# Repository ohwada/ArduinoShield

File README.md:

Arduino Shield
===============

Eagle data for Milling machine <br>
Arduino skech <br>

### LED 3x3 Matrix No1
https://github.com/ohwada/ArduinoShield/tree/master/docs/led_3x3_1/ <br>

### LED 3x3 Matrix No2
https://github.com/ohwada/ArduinoShield/tree/master/docs/led_3x3_2/ <br>

### LED 3x3 Matrix No3
https://github.com/ohwada/ArduinoShield/tree/master/docs/led_3x3_3/ <br>

### Seven-Segment LED - SND2537
https://github.com/ohwada/ArduinoShield/tree/master/docs/7seg_snd2537/ <br>

### LED Button controlled by Serial
https://github.com/ohwada/ArduinoShield/tree/master/docs/led_button_1/ <br>

### ESP8266 CEREVO 
https://github.com/ohwada/ArduinoShield/tree/master/docs/led_button_1/ <br>

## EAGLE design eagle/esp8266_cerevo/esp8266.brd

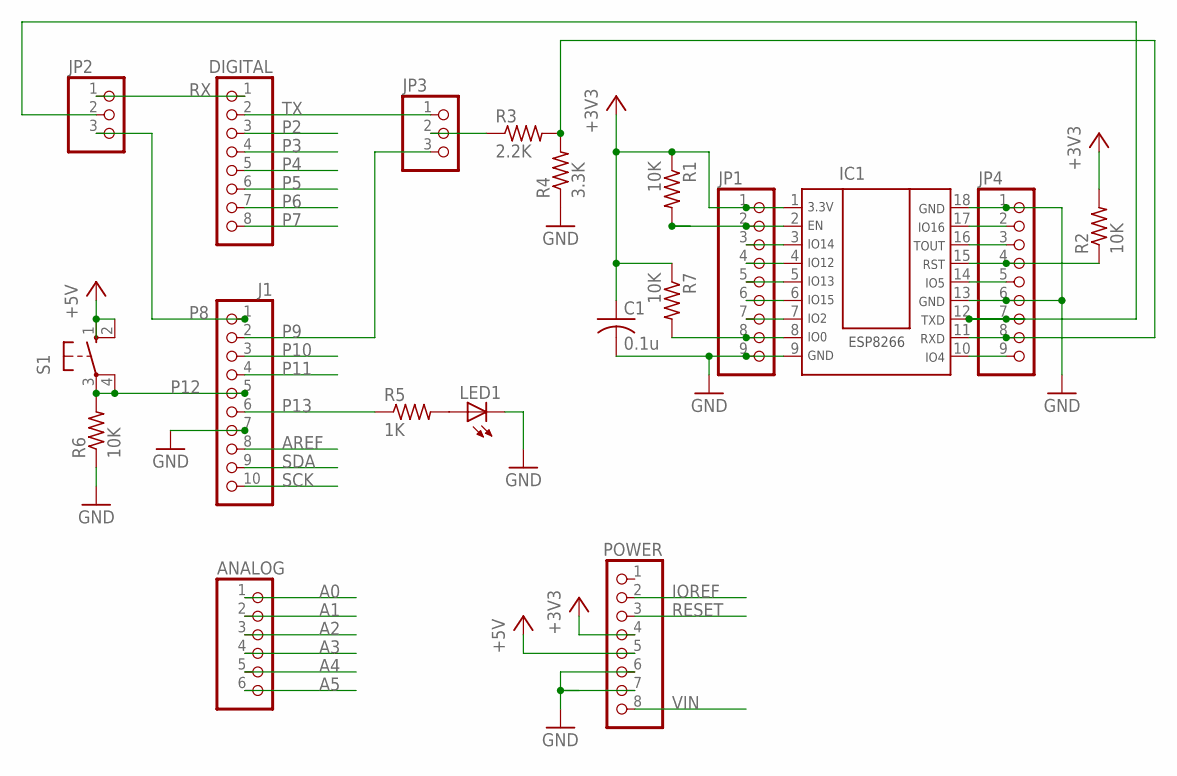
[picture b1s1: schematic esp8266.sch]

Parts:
ANALOG: PINHD-1X6; 1X06
C1: 0.1u; C050-025X075
DIGITAL: PINHD-1X8TH; 1X08-TH
IC1: ESP8266; CEREVO-PKG
J1: PINHD-1X10TH; 1X10-TH
JP1, JP4: PINHD-1X9; 1X09
JP2, JP3: PINHD-1X3; 1X03
LED1: LED3MM
POWER: PINHD-1X8TH; 1X08-TH
R1, R2, R6, R7: 10K; 0207/10
R3: 2.2K; 0207/10
R4: 3.3K; 0207/10
R5: 1K; 0207/10
S1: 10-XX; B3F-10XX

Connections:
+3V3: C1.1, IC1.1, JP1.1, POWER.4, R1.1, R2.2, R7.1
+5V: POWER.5, S1.1 (S), S1.2 (S1)
A0: ANALOG.1
A1: ANALOG.2
A2: ANALOG.3
A3: ANALOG.4
A4: ANALOG.5
A5: ANALOG.6
AREF: J1.8
GND: C1.2, IC1.9, IC1.13, IC1.18, J1.7, JP1.9, JP4.1, JP4.6, LED1.K (C), POWER.6, POWER.7, R4.1, R6.1
IOREF: POWER.2
unnamed: IC1.11, JP4.8, R3.2, R4.2
unnamed: LED1.A, R5.2
unnamed: JP3.2, R3.1
unnamed: IC1.12, JP2.2, JP4.7
unnamed: IC1.2, JP1.2, R1.2
unnamed: IC1.15, JP4.4, R2.1
unnamed: IC1.3, JP1.3
unnamed: IC1.4, JP1.4
unnamed: IC1.5, JP1.5
unnamed: IC1.6, JP1.6
unnamed: IC1.7, JP1.7
unnamed: IC1.8, JP1.8, R7.2
unnamed: IC1.10, JP4.9
unnamed: IC1.17, JP4.2
unnamed: IC1.16, JP4.3
unnamed: IC1.14, JP4.5
P2: DIGITAL.3
P3: DIGITAL.4
P4: DIGITAL.5
P5: DIGITAL.6
P6: DIGITAL.7
P7: DIGITAL.8
P8: J1.1, JP2.3
P9: J1.2, JP3.3
P10: J1.3
P11: J1.4
P12: J1.5, R6.2, S1.3, S1.4 (P1)
P13: J1.6, R5.1
RESET: POWER.3
RX: DIGITAL.1, JP2.1
SCK: J1.10
SDA: J1.9
TX: DIGITAL.2, JP3.1
VIN: POWER.8

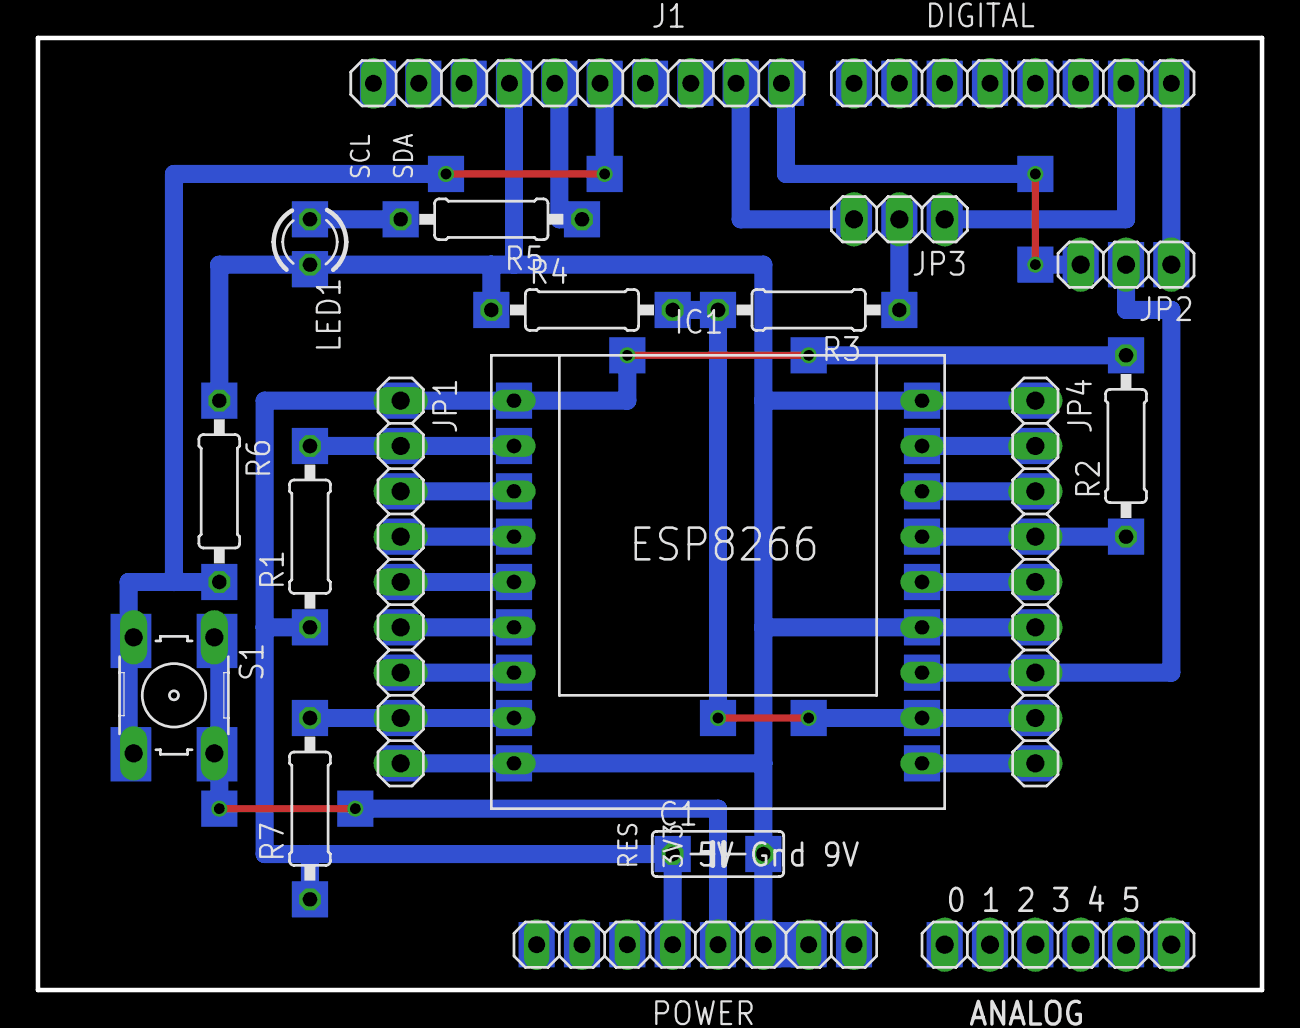
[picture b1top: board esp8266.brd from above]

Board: 2 copper layers, 68.6 x 53.3 mm, 19 parts (0 on the bottom side), 25 nets.

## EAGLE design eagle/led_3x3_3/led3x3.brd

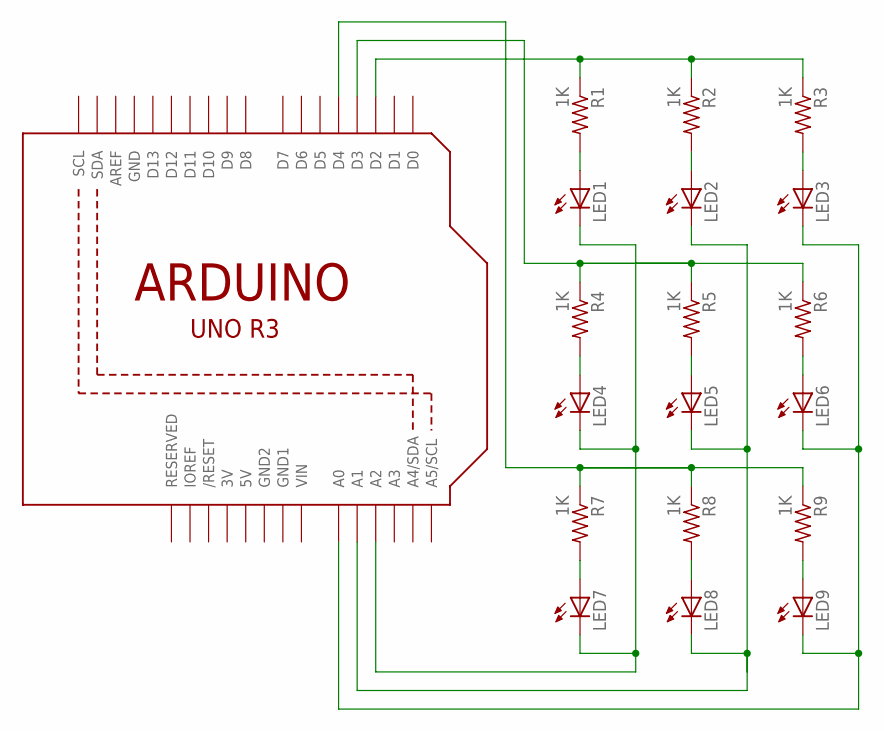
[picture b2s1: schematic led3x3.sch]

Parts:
LED1, LED2, LED3, LED4, LED5, LED6, LED7, LED8, LED9: LED5MM
R1, R2, R3, R4, R5, R6, R7, R8, R9: 1K; 0207/10
U1: ARDUINOR3-BPLACE

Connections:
3V: U1.3V
5V: U1.5V
D3: R4.1, R5.1, R6.1, U1.D3
GND: U1.GND
GND1: U1.GND1
GND2: U1.GND2
unnamed: LED3.K (C), LED6.K (C), LED9.K (C), U1.A0
unnamed: LED1.A, R1.2
unnamed: LED2.K (C), LED5.K (C), LED8.K (C), U1.A1
unnamed: R1.1, R2.1, R3.1, U1.D2
unnamed: LED2.A, R2.2
unnamed: R7.1, R8.1, R9.1, U1.D4
unnamed: LED1.K (C), LED4.K (C), LED7.K (C), U1.A2
unnamed: LED3.A, R3.2
unnamed: LED4.A, R4.2
unnamed: LED5.A, R5.2
unnamed: LED6.A, R6.2
unnamed: LED7.A, R7.2
unnamed: LED8.A, R8.2
unnamed: LED9.A, R9.2
VIN: U1.VIN

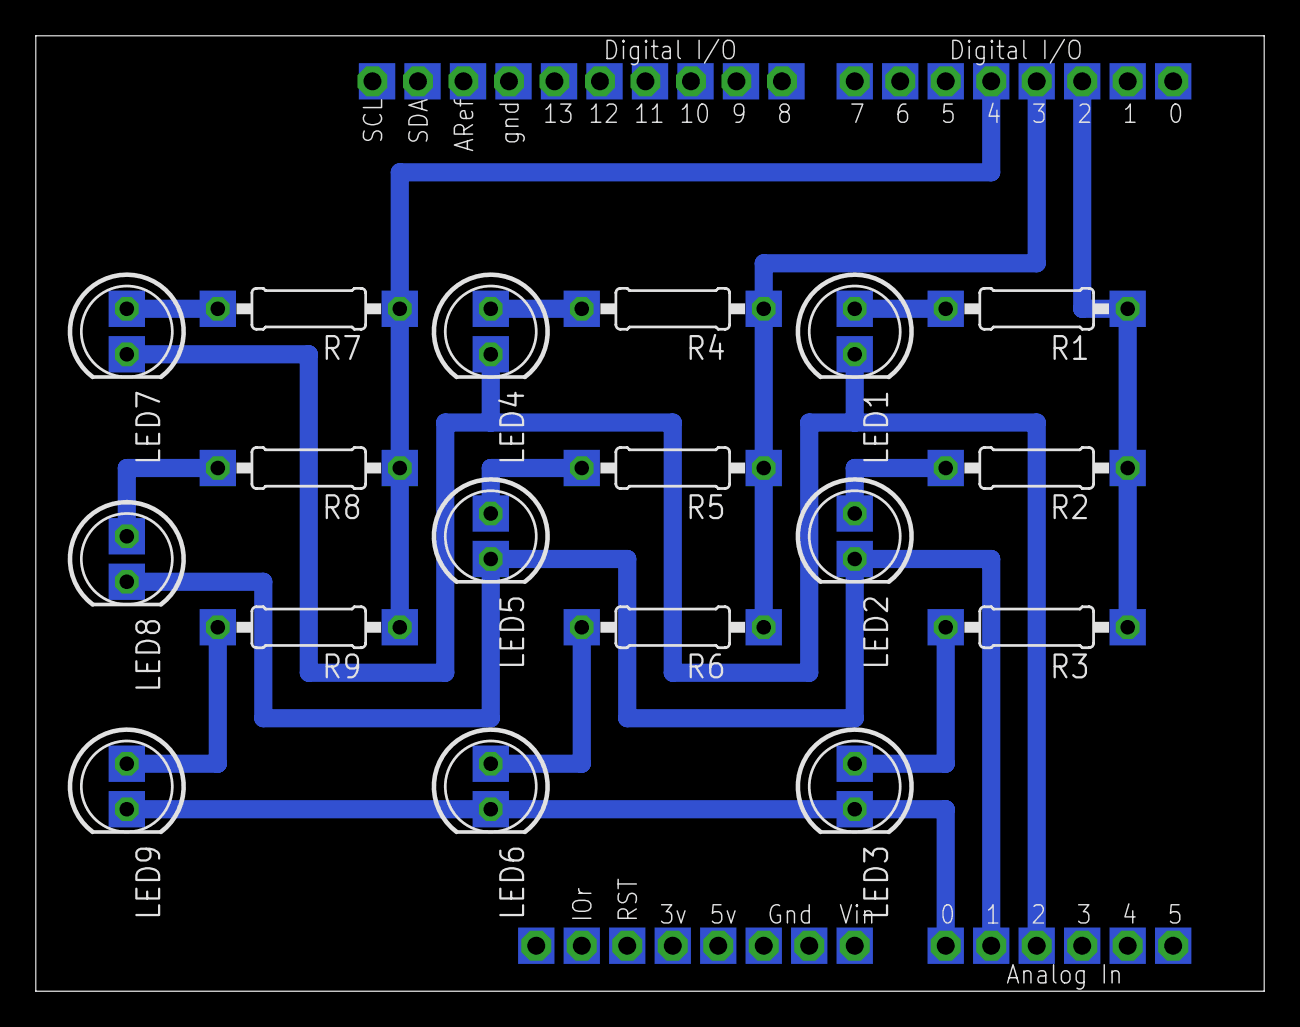
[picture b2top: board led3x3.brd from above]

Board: 2 copper layers, 68.6 x 53.3 mm, 19 parts (0 on the bottom side), 15 nets.

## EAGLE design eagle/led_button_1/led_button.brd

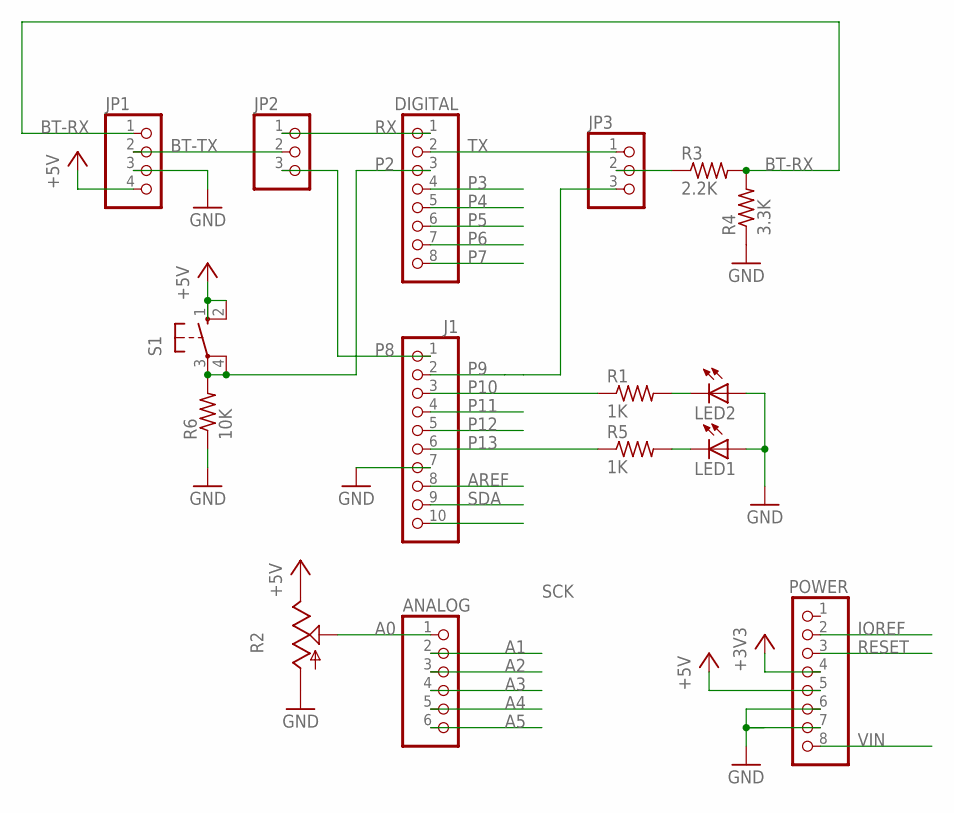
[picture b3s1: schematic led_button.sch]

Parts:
ANALOG: PINHD-1X6; 1X06
DIGITAL: PINHD-1X8TH; 1X08-TH
J1: PINHD-1X10TH; 1X10-TH
JP1: PINHD-1X4; 1X04
JP2, JP3: PINHD-1X3; 1X03
LED1, LED2: LED3MM
POWER: PINHD-1X8TH; 1X08-TH
R1, R5: 1K; 0207/10
R2: TRIM_US-B25P; B25P
R3: 2.2K; 0207/10
R4: 3.3K; 0207/10
R6: 10K; 0207/10
S1: 10-XX; B3F-10XX

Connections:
+3V3: POWER.4
+5V: JP1.4, POWER.5, R2.E, S1.1 (S), S1.2 (S1)
A0: ANALOG.1, R2.S
A1: ANALOG.2
A2: ANALOG.3
A3: ANALOG.4
A4: ANALOG.5
A5: ANALOG.6
AREF: J1.8
BT-RX: JP1.1, R3.2, R4.2
BT-TX: JP1.2, JP2.2
GND: J1.7, JP1.3, LED1.A, LED2.A, POWER.6, POWER.7, R2.A, R4.1, R6.1
IOREF: POWER.2
unnamed: LED1.K (C), R5.2
unnamed: JP3.2, R3.1
unnamed: LED2.K (C), R1.2
P2: DIGITAL.3, R6.2, S1.3, S1.4 (P1)
P3: DIGITAL.4
P4: DIGITAL.5
P5: DIGITAL.6
P6: DIGITAL.7
P7: DIGITAL.8
P8: J1.1, JP2.3
P9: J1.2, JP3.3
P10: J1.3, R1.1
P11: J1.4
P12: J1.5
P13: J1.6, R5.1
RESET: POWER.3
RX: DIGITAL.1, JP2.1
SCK: J1.10
SDA: J1.9
TX: DIGITAL.2, JP3.1
VIN: POWER.8

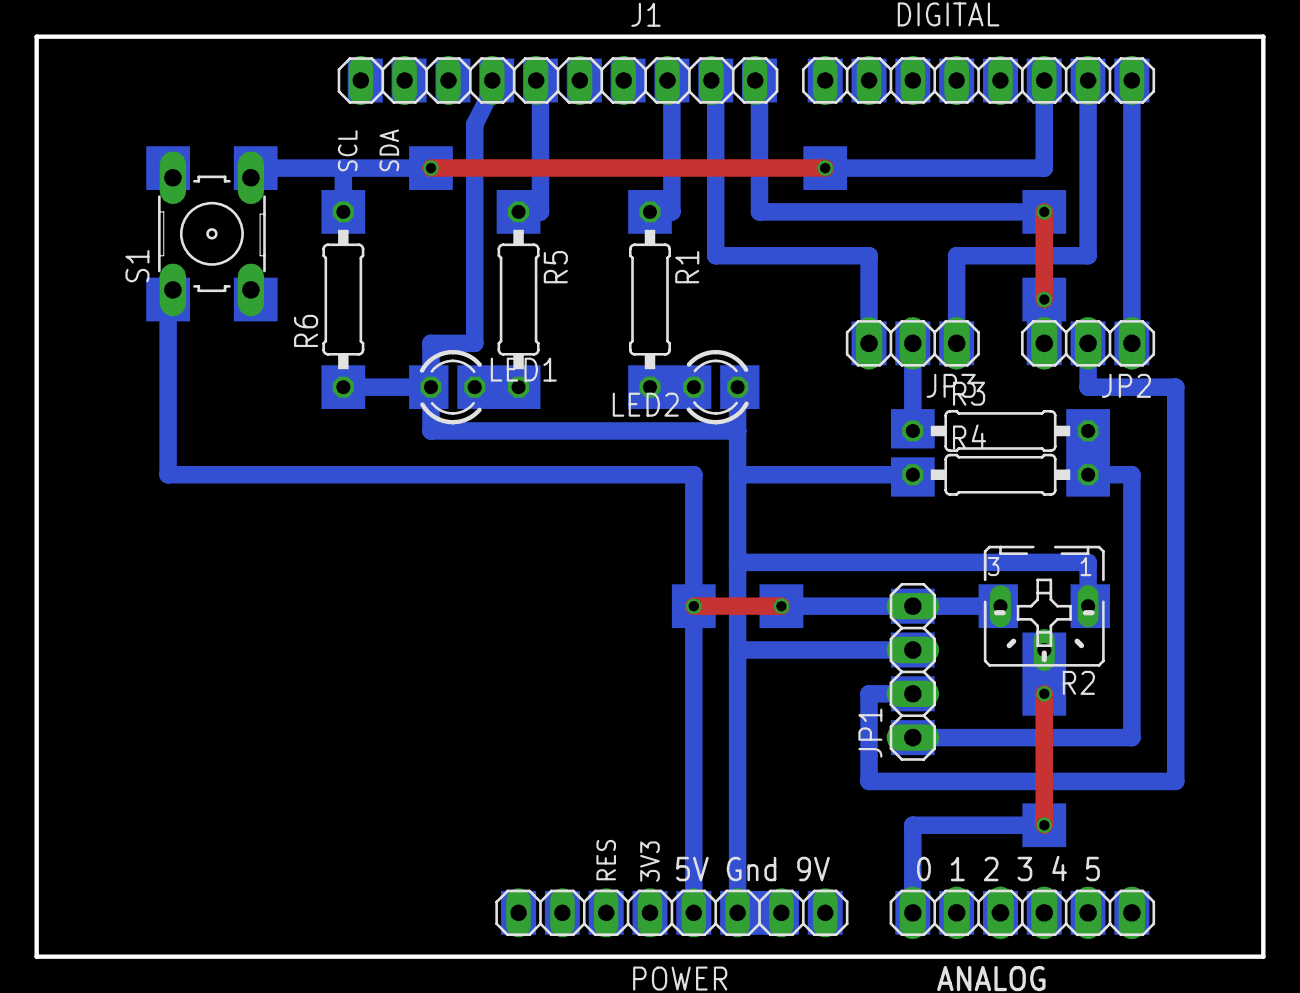
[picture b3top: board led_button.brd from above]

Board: 2 copper layers, 71.1 x 53.3 mm, 16 parts (0 on the bottom side), 15 nets.

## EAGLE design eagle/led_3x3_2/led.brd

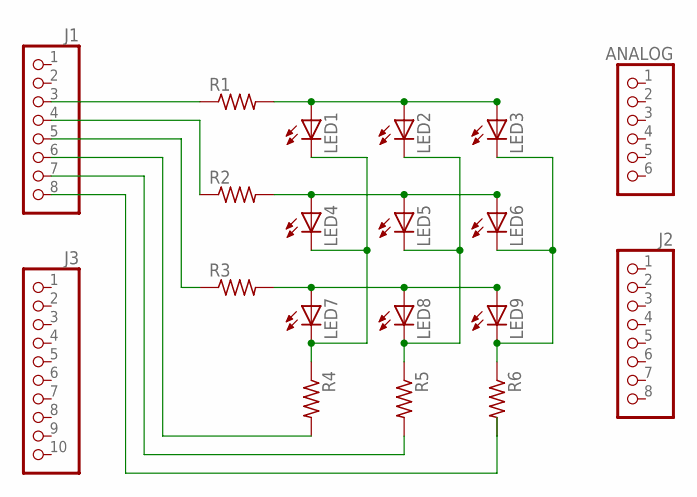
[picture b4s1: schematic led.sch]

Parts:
ANALOG: PINHD-1X6; 1X06
J1, J2: PINHD-1X8TH; 1X08-TH
J3: PINHD-1X10TH; 1X10-TH
LED1, LED2, LED3, LED4, LED5, LED6, LED7, LED8, LED9: LED3MM
R1, R2, R3, R4, R5, R6: R-US_0207/10; 0207/10

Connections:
unnamed: LED1.A, LED2.A, LED3.A, R1.2
unnamed: J1.3, R1.1
unnamed: LED4.A, LED5.A, LED6.A, R2.2
unnamed: LED7.A, LED8.A, LED9.A, R3.2
unnamed: LED3.K (C), LED6.K (C), LED9.K (C), R6.1
unnamed: LED2.K (C), LED5.K (C), LED8.K (C), R5.1
unnamed: J1.5, R3.1
unnamed: J1.4, R2.1
unnamed: LED1.K (C), LED4.K (C), LED7.K (C), R4.1
unnamed: J1.6, R4.2
unnamed: J1.7, R5.2
unnamed: J1.8, R6.2

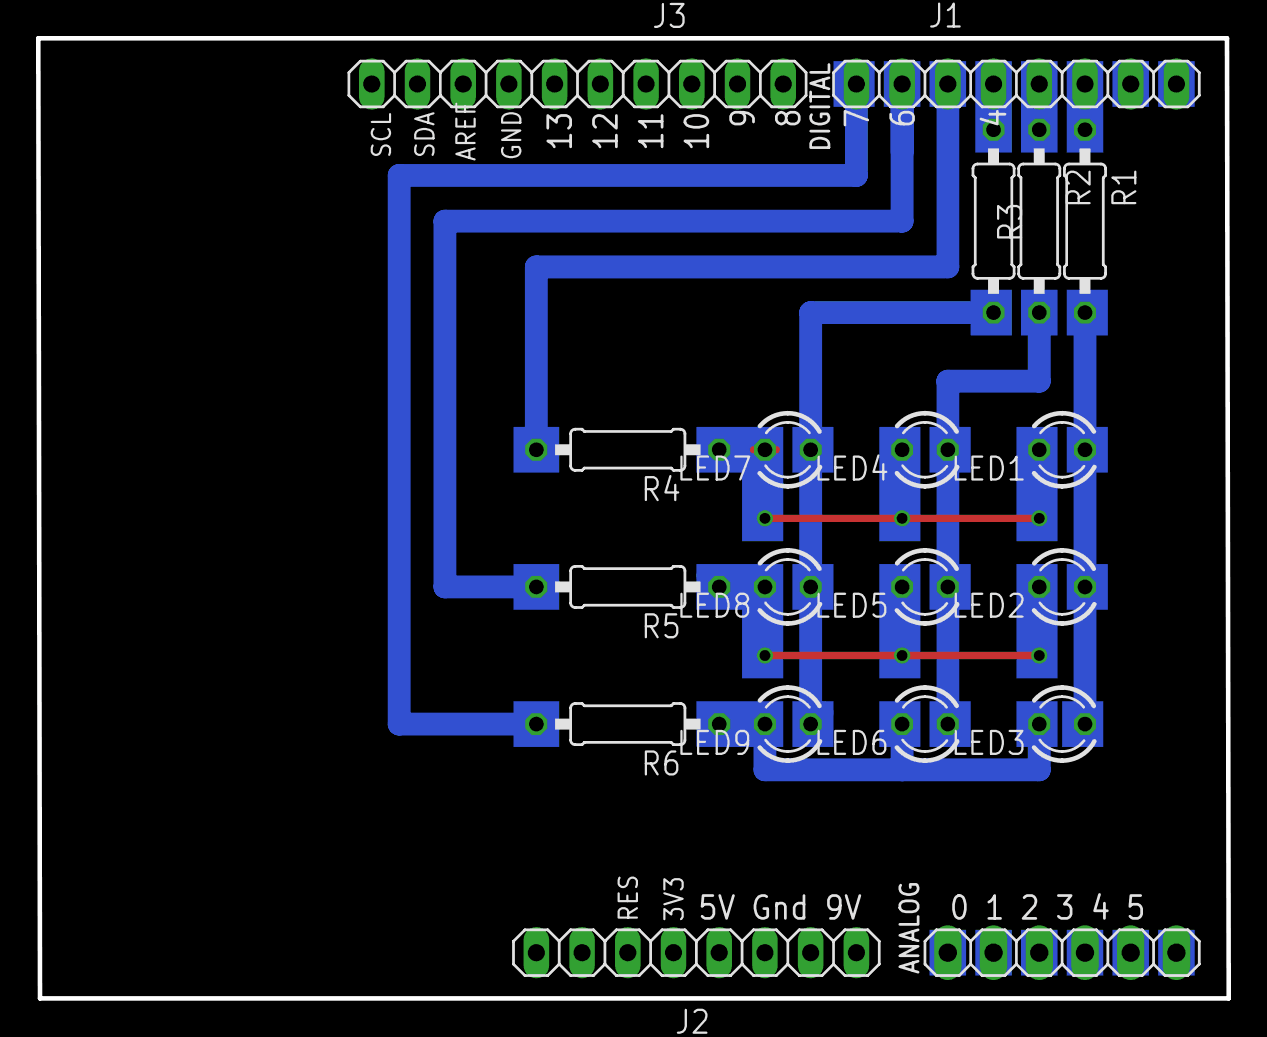
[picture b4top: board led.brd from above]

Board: 2 copper layers, 66.1 x 53.3 mm, 19 parts (0 on the bottom side), 12 nets.

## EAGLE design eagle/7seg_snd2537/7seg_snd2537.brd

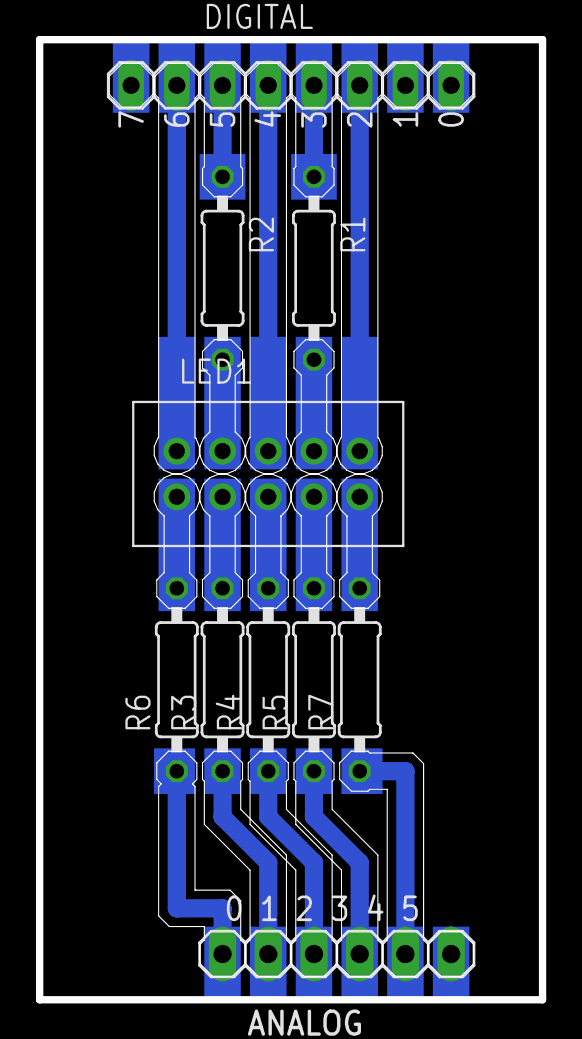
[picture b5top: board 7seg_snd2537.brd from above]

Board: 2 copper layers, 27.9 x 53.3 mm, 10 parts (0 on the bottom side), 17 nets.

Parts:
ANALOG: 1X06
DIGITAL: 1X08-TH
LED1: SND2537; SND2537-PKG
R1, R2, R3, R4, R5, R6, R7: 0207/10

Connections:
A0: ANALOG.1, R6.1
A1: ANALOG.2, R3.1
A2: ANALOG.3, R4.1
A3: ANALOG.4, R5.1
A4: ANALOG.5, R7.1
unnamed: LED1.7, R1.2
unnamed: LED1.9, R2.2
unnamed: LED1.2, R3.2
unnamed: LED1.3, R4.2
unnamed: LED1.4, R5.2
unnamed: LED1.1, R6.2
unnamed: LED1.5, R7.2
P2: DIGITAL.3, LED1.6
P3: DIGITAL.4, R1.1
P4: DIGITAL.5, LED1.8
P5: DIGITAL.6, R2.1
P6: DIGITAL.7, LED1.10

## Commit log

2015-02-28 snd2536
2015-03-01 FirstVersion
2015-04-09 LED Button
2015-05-19 add blog info
2015-05-19 bluetooth
2015-07-09 LED_3x3_3
2015-08-27 ESP8266 CEREVO
